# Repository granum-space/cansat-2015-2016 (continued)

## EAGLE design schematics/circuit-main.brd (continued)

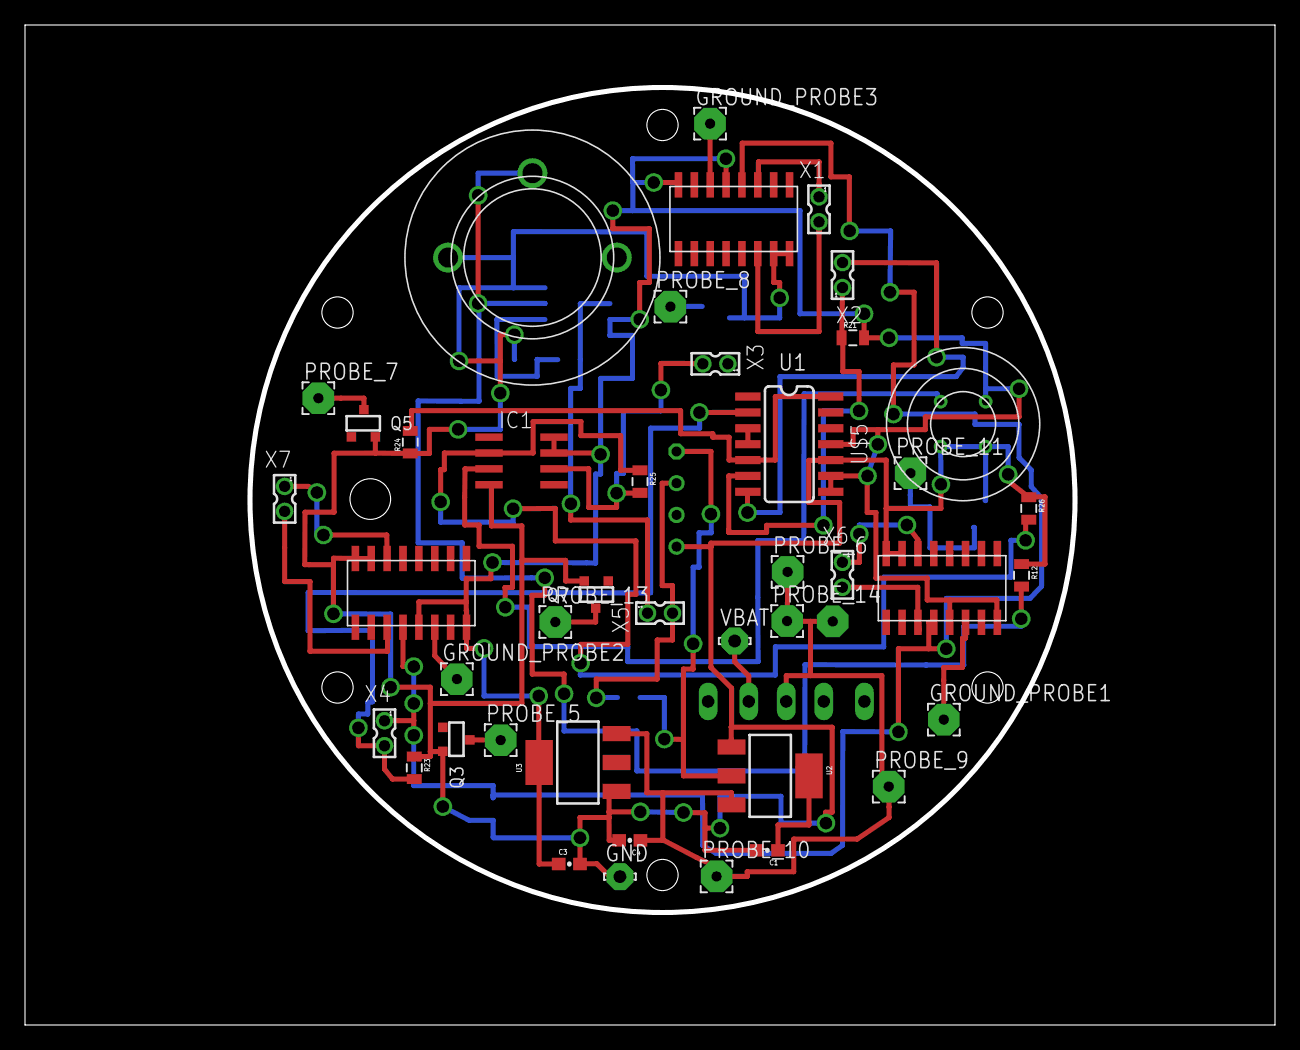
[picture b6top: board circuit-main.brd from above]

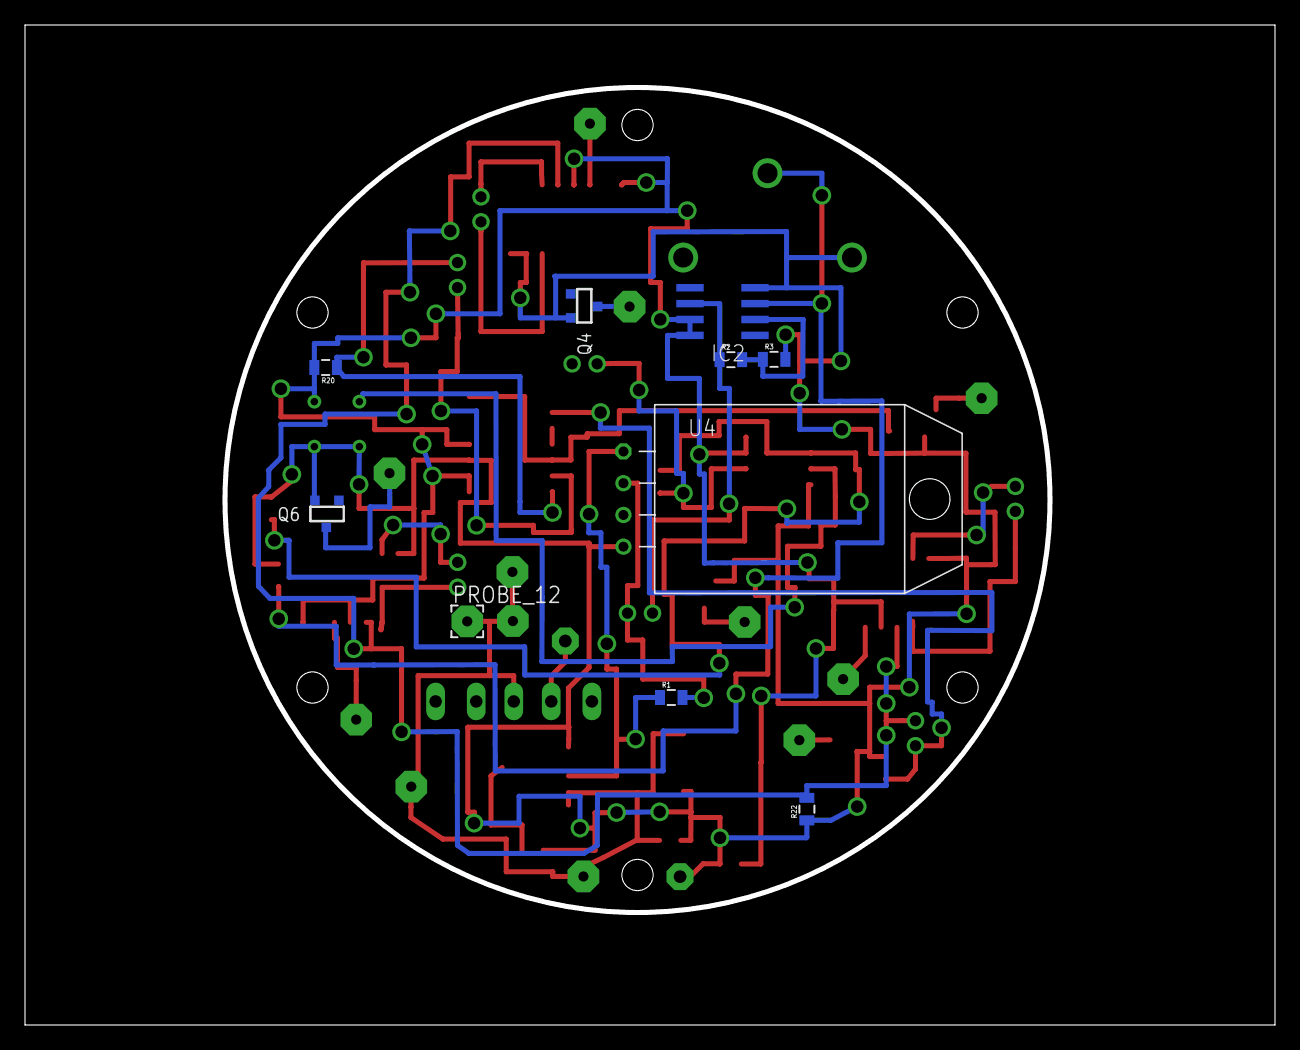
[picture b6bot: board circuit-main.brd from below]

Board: 2 copper layers, 100.0 x 80.0 mm, 53 parts (10 on the bottom side), 31 nets.

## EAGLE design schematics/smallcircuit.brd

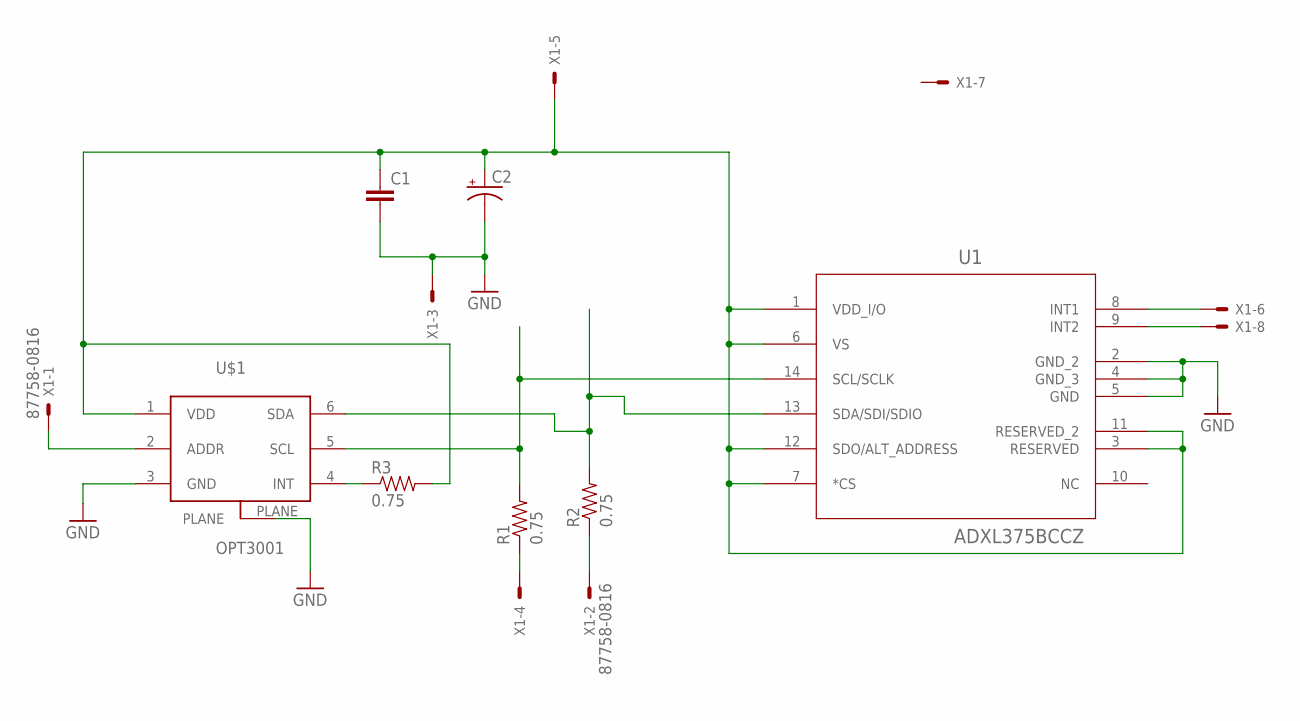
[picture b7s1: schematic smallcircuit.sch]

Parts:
C1: C-EUC0603; C0603
C2: CAP_POL3528; EIA3528
R1, R2, R3: 0.75; 0805
U1: ADXL375BCCZ; LGA_CC-14-1
U$1: OPT3001
X1: 87758-0816

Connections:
3.3V: C1.1, C2.A (+), R3.2, U1.1 (VDD_I/O), U1.3 (RESERVED), U1.6 (VS), U1.7 (*CS), U1.11 (RESERVED_2), U1.12 (SDO/ALT_ADDRESS), U$1.1 (VDD), X1.5
GND: C1.2, C2.C (-), U1.2 (GND_2), U1.4 (GND_3), U1.5 (GND), U$1.3 (GND), U$1.PLANE, X1.3
unnamed: U$1.2 (ADDR), X1.1
unnamed: R2.2, U1.13 (SDA/SDI/SDIO), U$1.6 (SDA)
unnamed: U1.8 (INT1), X1.6
unnamed: R1.1, X1.4
unnamed: R1.2, U1.14 (SCL/SCLK), U$1.5 (SCL)
unnamed: R3.1, U$1.4 (INT)
unnamed: R2.1, X1.2
unnamed: U1.9 (INT2), X1.8

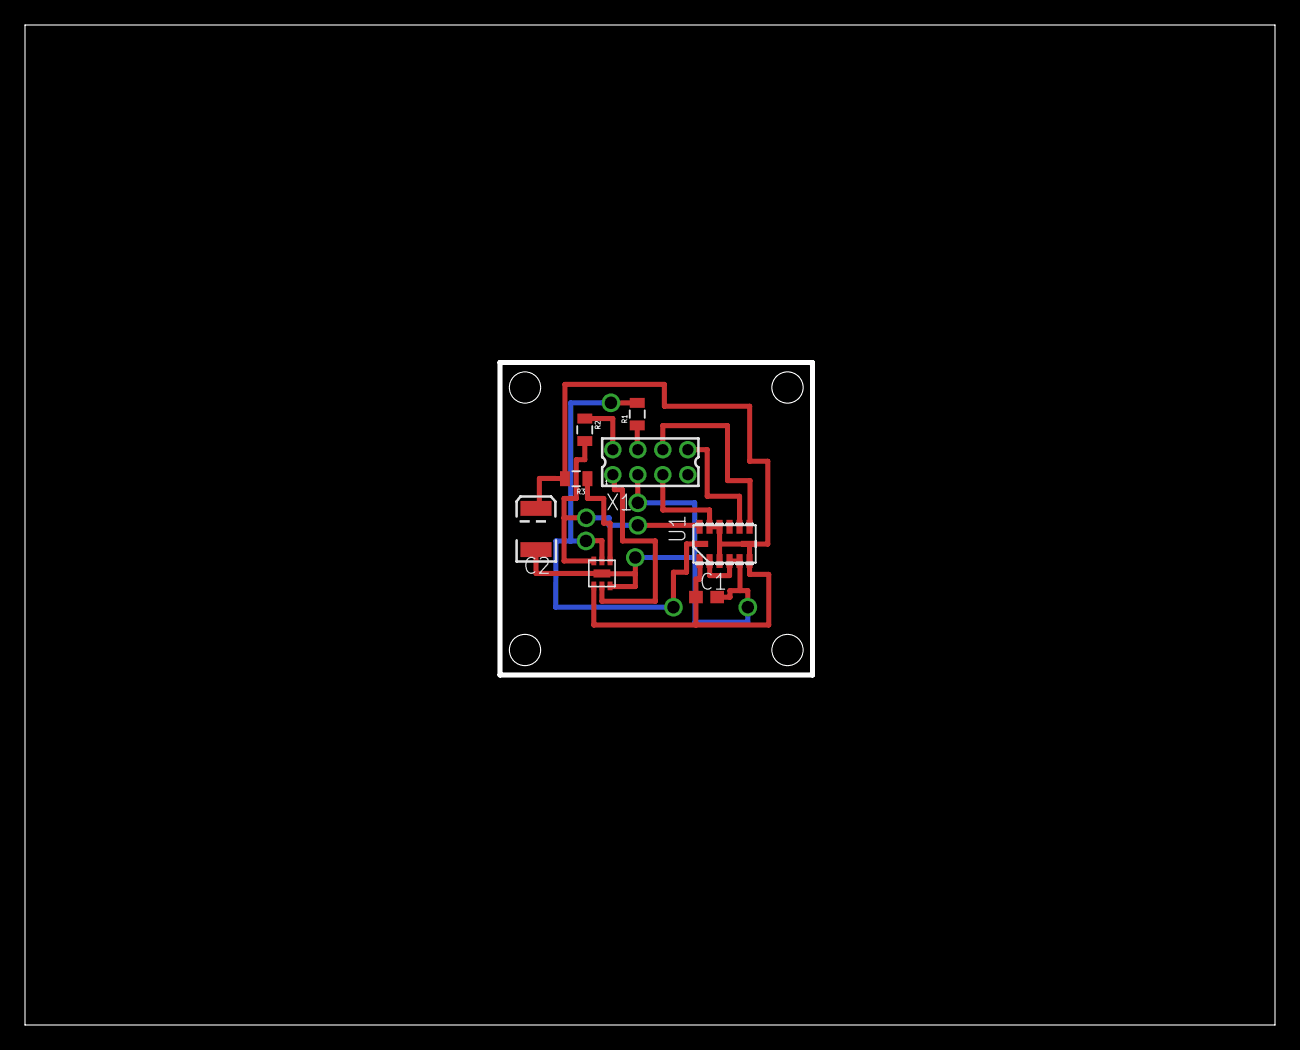
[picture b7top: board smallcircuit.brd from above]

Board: 2 copper layers, 100.0 x 80.0 mm, 8 parts (0 on the bottom side), 10 nets.

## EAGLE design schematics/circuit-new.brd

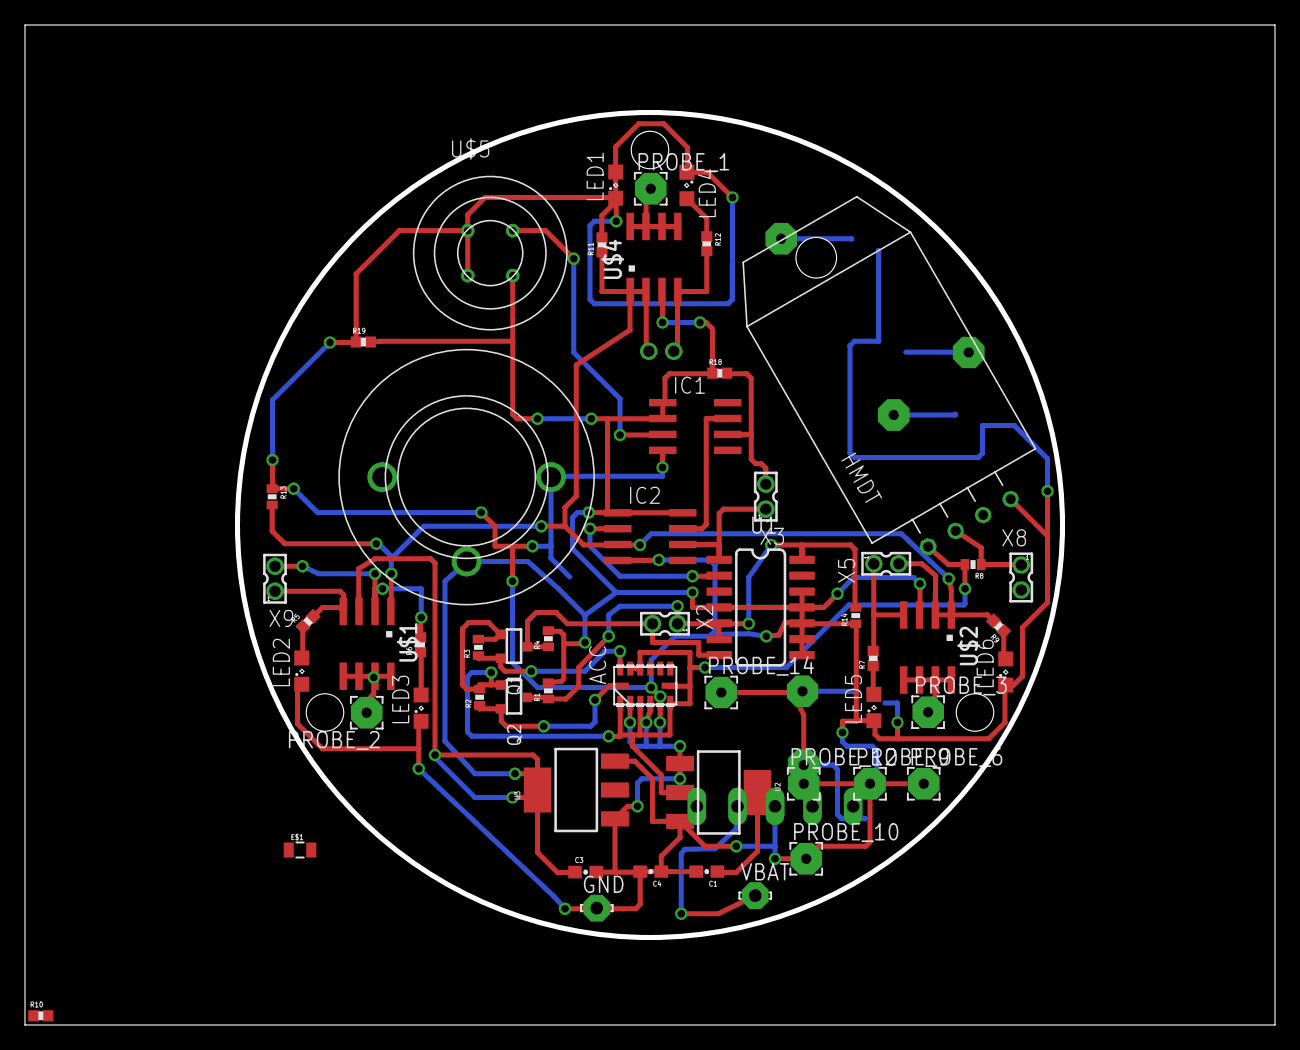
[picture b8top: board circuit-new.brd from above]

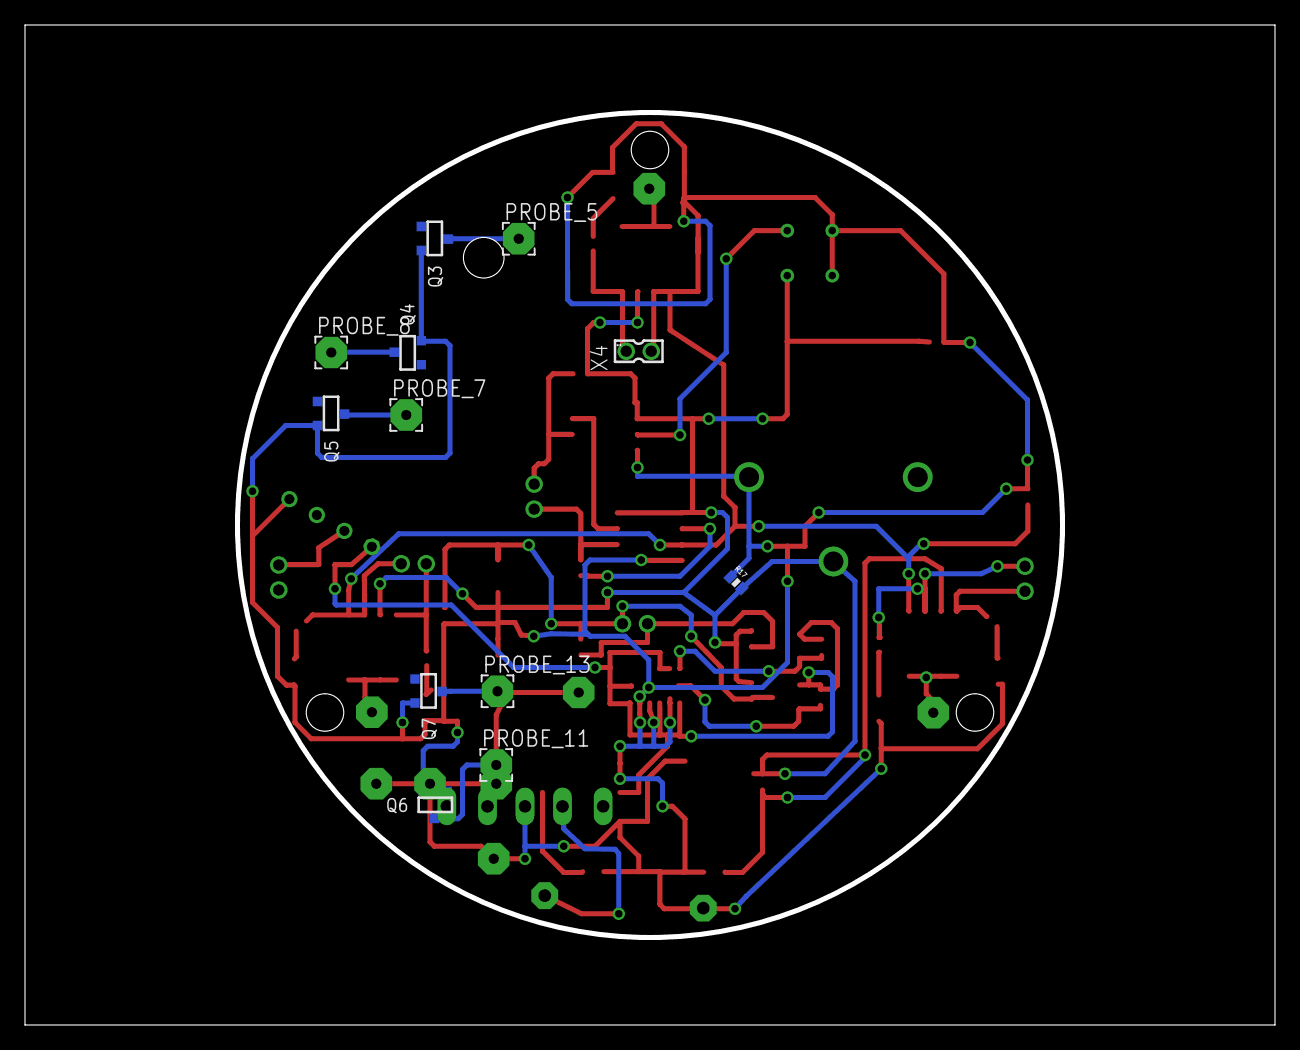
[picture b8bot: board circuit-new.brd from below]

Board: 2 copper layers, 100.0 x 80.0 mm, 68 parts (13 on the bottom side), 37 nets.

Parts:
ACC: ADXL375BCCZ; LGA_CC-14-1
C1, C3, C4: 4.7pF; 0603-CAP
E$1: 0805
GND: LSP10
HMDT: RHT03_DHT-22/RA
IC1, IC2: TLC271D; SO08
LED1, LED2, LED3, LED4, LED5, LED6: SML0805
PROBE_1, PROBE_2, PROBE_3, PROBE_5, PROBE_6, PROBE_7, PROBE_8, PROBE_9, PROBE_10, PROBE_11, PROBE_12, PROBE_13, PROBE_14: 2,54/0,8
Q1, Q2, Q3, Q4, Q5, Q6, Q7: SOT-23
R1, R2, R3, R4, R8: 10k; 0402-RES
R5, R6, R7, R9, R10, R11, R12, R18, R19: 10; 0402-RES
R13, R14, R17: 0402-RES
U1: AD5241BRU1M-REEL7AD5241BRZ1M; SOIC-14
U2, U3: SOT223
U$1, U$2, U$4: AO4606; SOIC-8
U$5: TGS4161
U$6: O2-A2
U$9: SS-8
VBAT: LSP10
X2, X3, X4, X5, X8, X9: 87758-0216

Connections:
3.3V: ACC.1, ACC.3, ACC.6, ACC.7, ACC.11, ACC.12, C1.1, HMDT.VDD, Q1.1, Q2.1, R2.2, R3.2, R8.2, U2.2, U2.4
5V: C3.1, IC1.1, IC1.2, IC2.1, IC2.8, R1.2, R4.2, R17.2, R18.1, R19.2, U1.4, U1.8, U1.9, U1.11, U3.2, U3.4, U$1.3, U$2.3, U$4.3, U$5.1, U$6.VOUT
GND: ACC.2, ACC.4, ACC.5, C1.2, C3.2, C4.2, GND.MP, HMDT.GND, IC1.4, IC2.4, LED1.C, LED2.C, LED3.C, LED4.C, LED5.C, LED6.C, Q3.2, Q4.2, Q5.2, Q6.2, Q7.2, R13.1, R14.1, R17.1, R19.1, U1.10, U2.1, U3.1, U$5.3, U$5.4, U$6.GND
unnamed: LED4.A, R12.1
unnamed: PROBE_2.1, U$1.5, U$1.6, U$1.7, U$1.8
unnamed: HMDT.DATA, R8.1, X8.1
unnamed: LED1.A, R11.1
unnamed: IC2.3, R13.2, U$1.1, U$2.1, U$4.1
unnamed: R11.2, U$4.2, X4.2
unnamed: R12.2, U$4.4, X4.1
unnamed: LED2.A, R5.1
unnamed: R9.2, U$2.2, X5.2
unnamed: LED3.A, R6.1
unnamed: R5.2, U$1.4, X9.1
unnamed: LED5.A, R7.1
unnamed: R7.2, U$2.4, X5.1
unnamed: LED6.A, R9.1
unnamed: PROBE_1.1, U$4.5, U$4.6, U$4.7, U$4.8
unnamed: R6.2, U$1.2, X9.2
unnamed: PROBE_5.1, Q3.3
unnamed: IC2.6, U1.1, X3.1
unnamed: PROBE_3.1, U$2.5, U$2.6, U$2.7, U$2.8
unnamed: IC1.3, U$5.2
unnamed: PROBE_8.1, Q4.3
unnamed: IC1.6, R18.2, X3.2
unnamed: IC2.2, U1.2
unnamed: PROBE_7.1, Q5.3
unnamed: R14.2, U1.5, U1.14
unnamed: PROBE_11.1, Q6.3
unnamed: PROBE_13.1, Q7.3
unnamed: U$9.P2, VBAT.MP
SCL_3.3V: ACC.14, Q2.2, R2.1
SCL_5V: Q2.3, R1.1, U1.6, X2.1
SDA_3.3V: ACC.13, Q1.2, R3.1
SDA_5V: Q1.3, R4.1, U1.7, X2.2
V+: IC1.7, IC2.7
VBAT: C4.1, PROBE_6.1, PROBE_9.1, PROBE_10.1, PROBE_12.1, PROBE_14.1, U2.3, U3.3, U$9.COM

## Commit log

2016-03-19 Публикуем проект!
2016-03-19 Добавлены заголовочники для SPI, акселерометра.
2016-03-19 Добавлены файлы для работы с АЦП
2016-03-19 Добавила файлы программы для измерения температуры и влажности
2016-03-19 Добавлены burn.h и sr.h
2016-03-27 Добавлен spi.c temper.c и temper.h перенесены в папку src.
2016-03-27 Добавлен acc.c
2016-03-27 Добавлен .gitignore для фильтрации ненужных в репозитории файлов
2016-03-27 Добавлены электрические схемы
2016-03-28 Первичный коммит. Добавляем проект графического интерфейса наземной станции
2016-03-28 Немного изменено поведение интерфейса при растягивании.
2016-03-28 Удалена строчка с ошибкой
2016-03-28 добавлен кем-то сгенеренный gitignore добавлена библиотека jssc (https://github.com/scream3r/java-simple-serial-connector) версии 2.8.0
2016-03-29 Доделана вся работа с портом, в т.ч. закрытие
2016-03-29 Добавлен pkt_types.h (там задефайнены типы пакетов)
2016-03-30 Реализован парсинг пакетов, сделана часть вывода пакета на экран.
2016-03-30 Добавлена проверка контрольной суммы.
2016-03-30 Написал (на основе примера Василия) PacketParser, который в будущем будет использоваться. На данный момент пакеты обрабатываются старым путём, PacketParser не задействован.
2016-03-31 Обновленная версия схемы
2016-03-31 исправлена схема
2016-03-31 Начал обрабатывать всё через PacketParser, доделал до стадии корректного чека.
2016-04-01 Теперь пакеты нормально обрабатываютя и отображаются.
2016-04-02 добавлена библиотека с "самодельным" датчиком освещенности для эл.схемы
2016-04-02 Доделал отображение.
2016-04-02 внесены изменения в датчик освещенности для эл.схемы
2016-04-09 Более менее привел проект в порядок Начал работу с onewire устройствами
2016-04-09 Обновлена библиотека (добавлены O2-A2 и TGS4161) и схема
2016-04-12 [схемы] удалил лишнее и переместил на место то, что сбежало
2016-04-16 В эл.схему добавлен блок переключения стержней
2016-04-19 Исправил ошибки на схеме и переосмыслил её
    Добавил библиотеку с коннекторами (с разъемом для SD карты)
    Добавил библиотеку с датчиком влажности DHT022
    Добавил в библотеку elements
    GPS модуль KL3333
    Комплиментарную mosfet пару AO4606
    N-mosfet NTR4501N
2016-04-20 Добавил переключатель SS-8
2016-04-20 Добавил функции для расчета crc8
2016-04-22 Добавил GPS модуль UBLOX CAM-M8Q
2016-04-23 почти закончили схему (кроме пережигателей, термисторов, выключателей и флешки) + начала разводить плату
2016-04-23 добавил функции для работы с датчиком влажности и подправил 1wire
2016-04-25 Добавил шаблон функций работы с I2C
2016-04-25 Убрал заглушки под функции для работы с DHT022 в контексте onewire. Заглушил предупреждение компилятора о порядке скобок в сравнении
2016-04-25 Подправил оформление, добавил коды ошибок, комментарии. Требуется несколько исправлений (смотри комментарии к коммиту на гитхабе)
2016-04-26 Написал spi, начал писать интерфейс sd карты.
2016-04-30 Добавлена плата
2016-04-30 В схему добавлены пережигатели и выключатель + обновлена плата + начата работа с отдельной платой для gps
2016-05-01 Исправил пару мелких ошибок на схеме. Вынес регуляторы напряжения из спаркфановской библиотеки в нашу - elements и правильно объединил им выводы. Исправил символ для TGS* датчика CO2. Все элементы об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
2016-05-01 Чуть чуть подправил определения методов i2c
2016-05-02 Добавил запись на sd карту, функции для сброса пакетов (datautils.c)
2016-05-05 Начал работу с i2c
2016-05-07 Последняя версия платы и схемы
2016-05-07 Выхожу на финишную прямую с платой
2016-05-07 версия основной платы от 5.05.16
2016-05-07 Вышла на финишную прямую с основной платой Начата работа с платой gps
2016-05-07 Полностью разведена плата
2016-05-07 Удалила лишние локфайлы
2016-05-07 дописал I2C НАДО ЕЩЕ ПРАВИТЬ
2016-05-07 Переделана схема подключения стержней, в библиотеку добавлен MC74HC4051A, к датчику кислорода подключен операционный усилитель
2016-05-07 Добавил UART-DEBUG, который вечно забывают залить. Добил ошибки в I2C
2016-05-08 Полностью исправлена основная плата (заменены резисторы, изменен диаметр сквозных отверстий, добавлены новые элементы из схемы)
2016-05-14 Проделана работа с ацп
2016-05-14 Добавлена готовая плата gps (есть мелкие недочеты, которые в ближайшее время будут исправлены)
2016-05-15 Доделала плату gps
2016-05-15 Немного подраавил разводку (из соображений увеличения антенного полигона)
    Немного исправил свойства полигонов (подключение к GND, создание "сиротливых полигонов" и поправил в DRC отступы от края платы
    Добавил задание на экспорт гербер файлов на печать плат
2016-05-16 Доделал многостраничную запись на sd карту.
2016-05-16 Полностью заменил uart_stdio на uart-debug, SPI теперь работает и на ATmega328p, и на ATmega128.
2016-05-17 Написал (не проверял) работу с радиомодулем, прикрепил к проекту наши uart.h и uart.c. Не могу собрать проект из-за ошибки в adc.c в строке 91.
2016-05-17 Исправил досадное упущение, не позволяющее компилировать проект
2016-05-18 добавляю плату с акселерометром и светодатчиком (OPT3001)
2016-05-20 В коммите содержатся все изменения, сделанные 19.05 для предзащиты.
2016-05-21 доделал crc в файле 1wdevices
2016-05-22 добавляю основную разведенную плату (переименована в circuit-main)
2016-05-22 добавляю основную плату (переименована в circuit-main)
2016-05-23 начала работу с gps
2016-05-23 почти написал работу с радиомодулем
2016-05-27 Чуть чуть починил радиомодуль. Почистил проект. Добавил конфиг
2016-05-27 Еще ошибки
2016-05-28 коммит
2016-05-28 код для дигипота
2016-05-28 Контрольный выстрел
2016-05-28 DHT22 доработан по реальному устройоству
2016-05-30 Изменения, сделанные перед видео.
2016-06-02 готовые 2 платы
2016-06-03 начал программировать опт
2016-06-06 Еще больше исправил dht22 по реальному устройству
2016-06-06 подлечил дигипот и временно убрал opt3001
2016-06-13 Платы новой концепции
2016-06-15 opt3001
2016-06-16 Правки платы для аналоговых устройств и доделана плата для I2C устройств
2016-06-18 Радиомодуль, sd карта работают.
2016-06-21 исправил OPT осталось немного доработать
2016-06-24 доделал опт осталось подставить правильный адресс датчика и подобрать конфигурацию
2016-06-25 Акселерометр работает.
2016-06-25 Платы, правки, накопленные изменения
2016-06-26 Сделано измерение сопротивления почвы.
2016-06-27 подправил опт осталось сделать функцию на измерение
2016-06-27 подравил опт
2016-06-28 добавил нижний предел и переделал main под тест (всё для опта)
2016-06-29 добавил нижний предел к опту и т п
2016-06-29 Мелкие изменения.
2016-06-29 опт доделан
2016-06-29 Служба времени, сопротивление почвы.
2016-06-29 Теперь все инициализаии проходят только один раз и другие мелкие изменения.
2016-06-29 объединил функции выхода из ракеты и чтения результата в одну
2016-06-30 Отмена предидущего коммита
2016-07-01 плата для пережигателей
2016-07-01 Предложение платы с пережигатели и DHT
2016-07-02 плата с пережигателями
2016-07-02 плата на печать
2016-07-02 Накопленные изменения.
2016-07-06 rc-1
2016-07-07 Этот код улетел ввысь!
